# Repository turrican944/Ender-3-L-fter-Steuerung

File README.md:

# Luefter-Steuerung
Lüfter Schalter Ender 3 Pro

Lüfter Schaltplatine für Ender 3 Pro und andere 3D Drucker mit ITS428 Highsideschalter.

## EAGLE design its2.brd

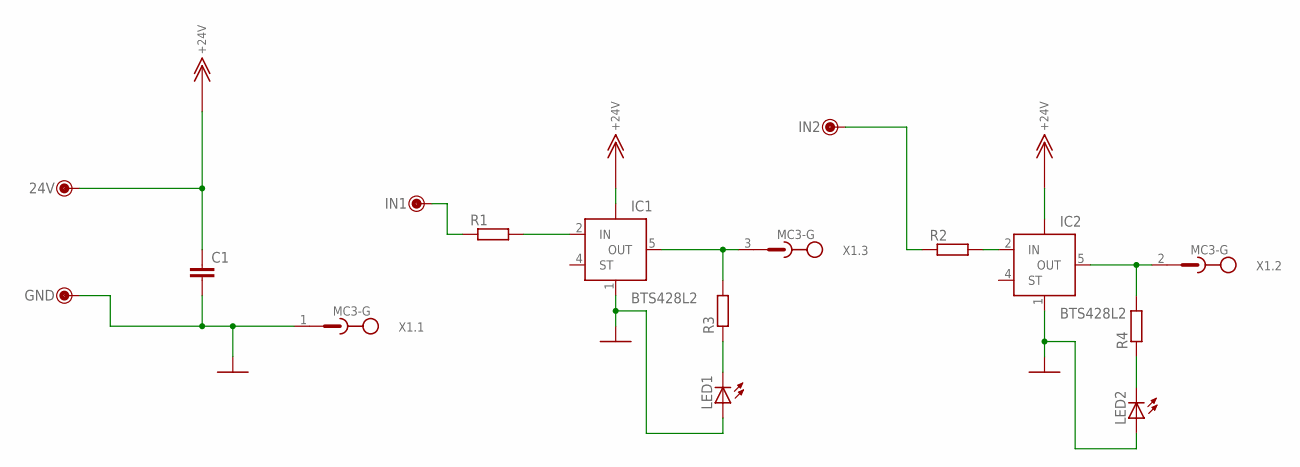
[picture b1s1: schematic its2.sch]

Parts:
24V: PINGERAD
C1: C-EUC0805K; C0805K
GND: PINGERAD
IC1, IC2: BTS428L2; TO252-5-11
IN1, IN2: PINGERAD
LED1, LED2: LEDSML1206; SML1206
R1, R2: R-EU_M0805; M0805
R3, R4: R-EU_R0805; R0805
X1: MC3-G

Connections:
+24V: 24V.1, C1.1, IC1.TAB (VBB), IC2.TAB (VBB)
GND: C1.2, GND.1, IC1.1 (GND), IC2.1 (GND), LED1.A, LED2.A, X1.1
unnamed: IN1.1, R1.1
unnamed: IC2.5 (OUT), R4.2, X1.2
unnamed: IC1.5 (OUT), R3.2, X1.3
unnamed: IN2.1, R2.1
unnamed: IC2.2 (IN), R2.2
unnamed: IC1.2 (IN), R1.2
unnamed: LED1.C, R3.1
unnamed: LED2.C, R4.1

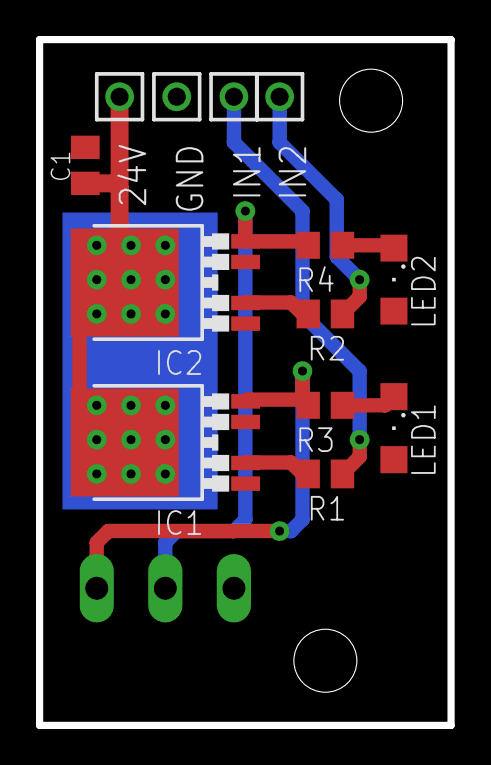
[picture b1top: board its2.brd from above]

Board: 2 copper layers, 22.9 x 38.1 mm, 14 parts (1 on the bottom side), 10 nets.

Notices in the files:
its2.brd:
CC BY-NC-SA 4.0
